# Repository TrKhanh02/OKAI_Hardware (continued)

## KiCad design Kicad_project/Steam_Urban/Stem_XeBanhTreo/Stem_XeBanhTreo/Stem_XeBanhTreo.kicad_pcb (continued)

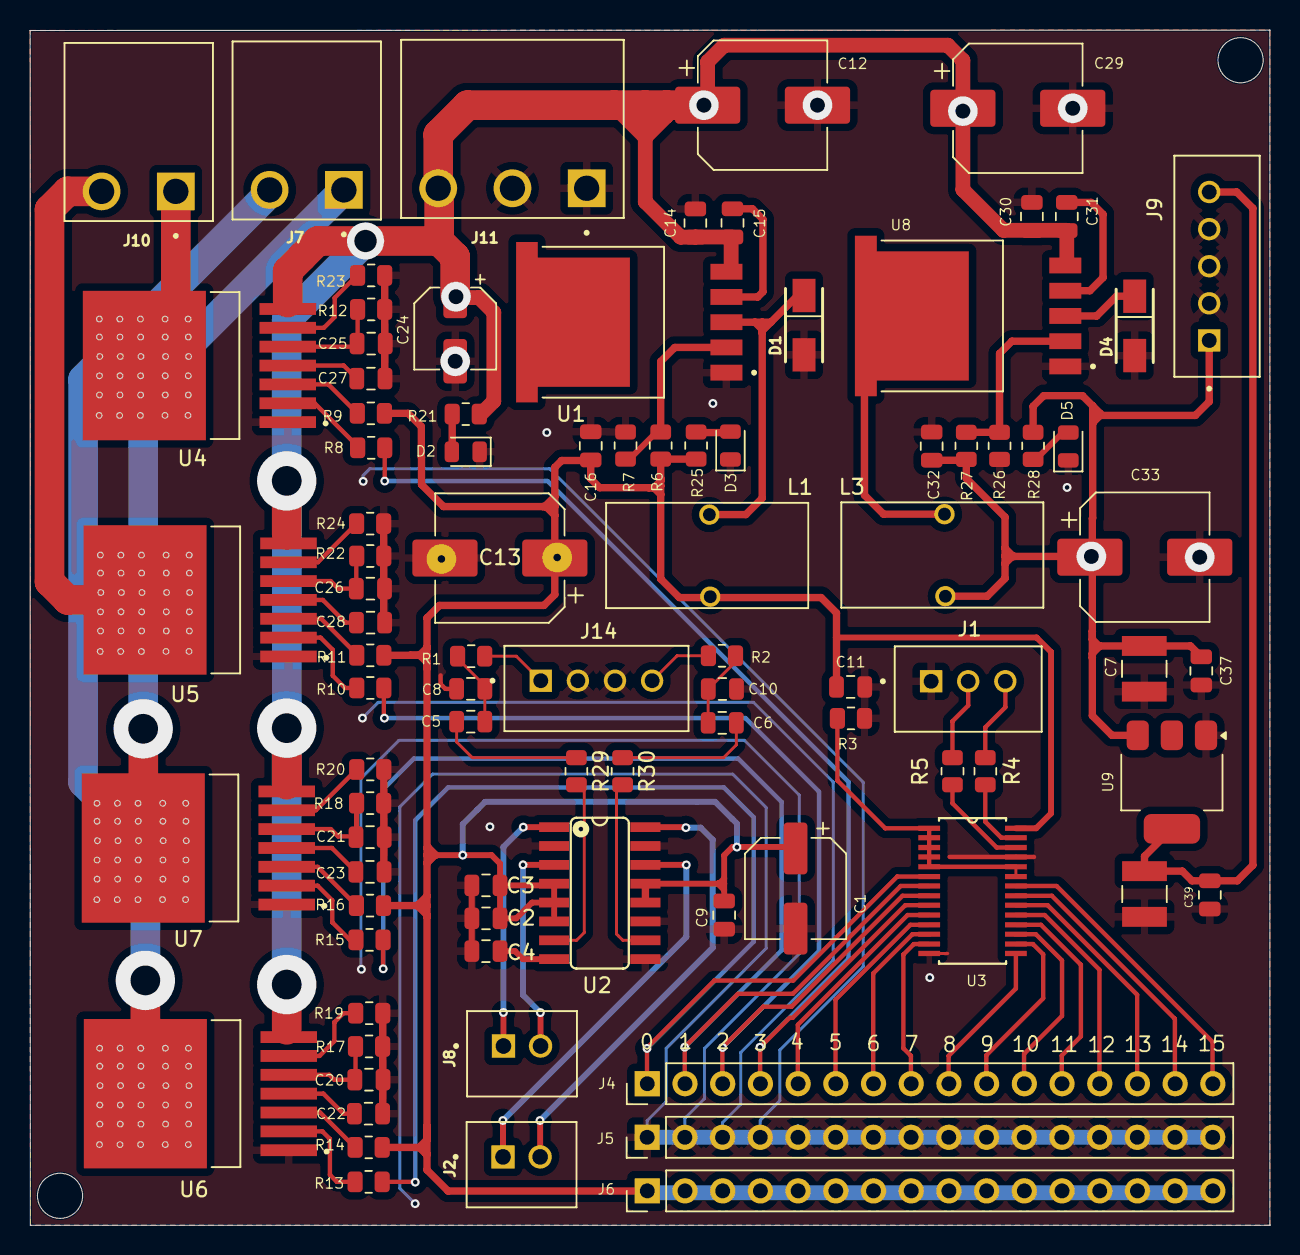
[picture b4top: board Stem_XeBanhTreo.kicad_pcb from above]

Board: 2 copper layers, 83.5 x 80.5 mm, 90 parts (0 on the bottom side), 68 nets.

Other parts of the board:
C17: 22uF/16V; CAPPC3528X210N
C39: 104; C_0805_2012Metric
J1: PCA9685; JST_B3B-XH-A
J14: B4B-XH-A; JST_B4B-XH-A

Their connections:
/SCL: J1.2; also elsewhere on the board
/SDA: J1.3; also elsewhere on the board
unnamed 32: J14.1; also elsewhere on the board
unnamed 33: J14.4; also elsewhere on the board

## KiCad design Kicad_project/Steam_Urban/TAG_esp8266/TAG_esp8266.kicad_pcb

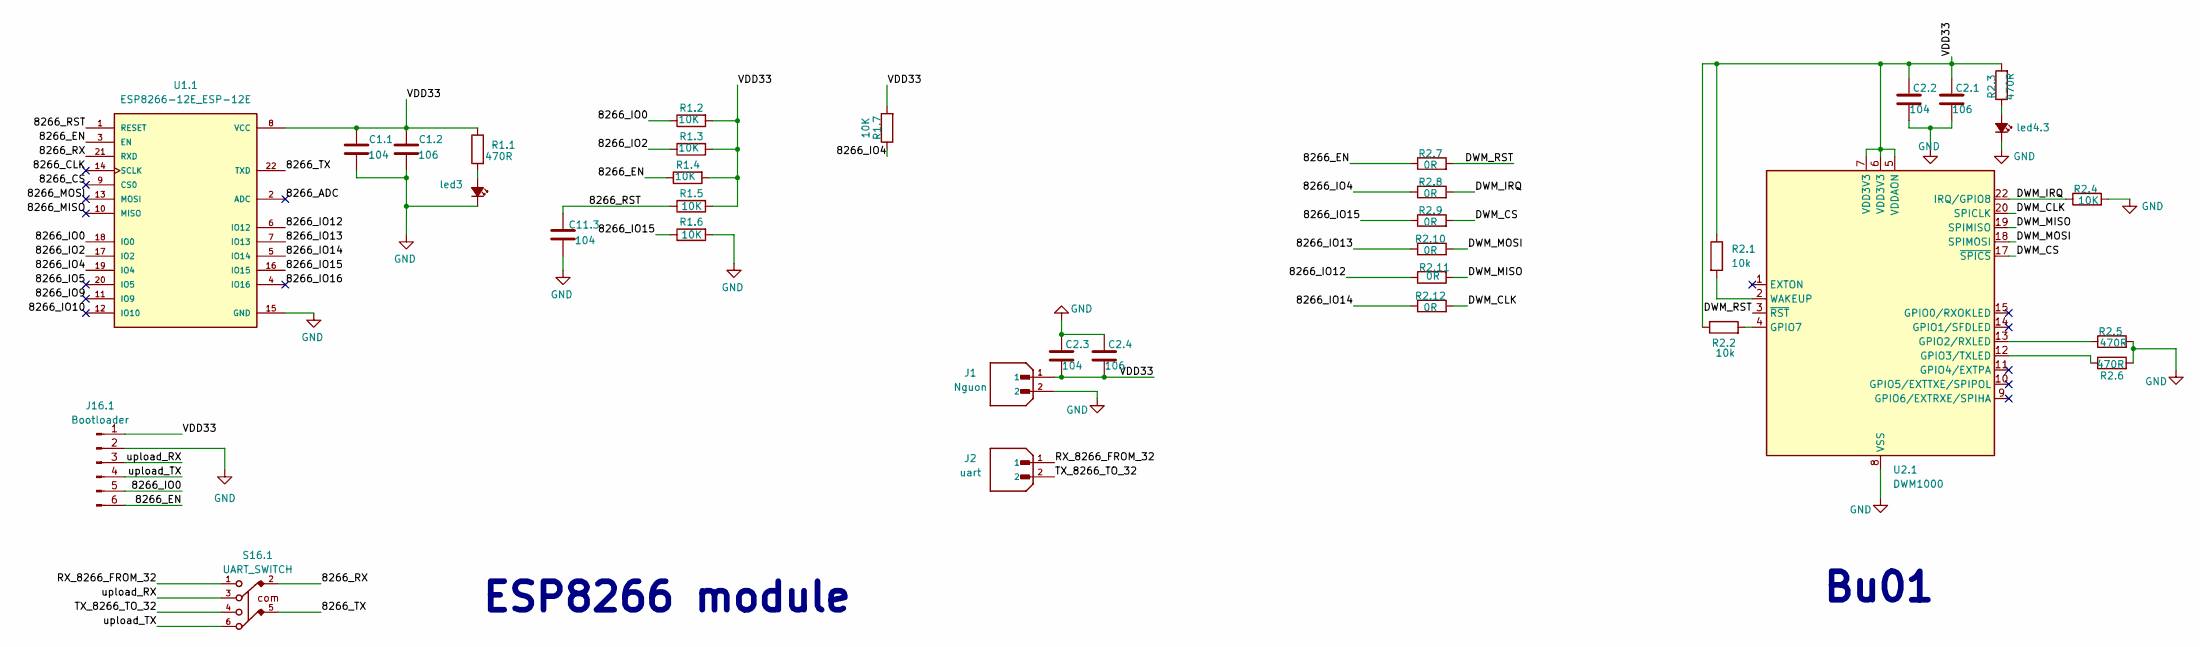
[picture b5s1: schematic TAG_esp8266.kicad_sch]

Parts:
C1.1, C2.2, C2.3, C11.3: 104; C_0805_2012Metric_Pad1.18x1.45mm_HandSolder
C1.2, C2.1, C2.4: 106; C_0805_2012Metric_Pad1.18x1.45mm_HandSolder
J1: Nguon; JST_B2B-XH-A_LF__SN_; PARTREV N/A
J2: uart; JST_B2B-XH-A_LF__SN_; PARTREV N/A
J16.1: Bootloader; PinSocket_1x06_P2.54mm_Vertical
R1.1, R2.3, R2.5, R2.6: 470R; R_0805_2012Metric_Pad1.20x1.40mm_HandSolder
R1.2, R1.3, R1.4, R1.5, R1.6, R1.7, R2.4: 10K; R_0805_2012Metric_Pad1.20x1.40mm_HandSolder
R2.1, R2.2: 10k; R_0805_2012Metric_Pad1.20x1.40mm_HandSolder
R2.7, R2.8, R2.9, R2.10, R2.11, R2.12: 0R; R_0805_2012Metric_Pad1.20x1.40mm_HandSolder
S16.1: UART_SWITCH; 452406020024
U1.1: ESP8266-12E_ESP-12E; XCVR_ESP8266-12E_ESP-12E
U2.1: DWM1000
led3, led4.3: LED_Small_Filled; LED_0805_2012Metric_Pad1.15x1.40mm_HandSolder

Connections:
/8266_ADC: U1.1.2 (ADC)
/8266_CLK: U1.1.14 (SCLK)
/8266_CS: U1.1.9 (CS0)
/8266_EN: J16.1.6, R1.4.1, R2.7.1, U1.1.3 (EN)
/8266_IO0: J16.1.5, R1.2.1, U1.1.18 (IO0)
/8266_IO2: R1.3.1, U1.1.17 (IO2)
/8266_IO4: R1.7.1, R2.8.1, U1.1.19 (IO4)
/8266_IO5: U1.1.20 (IO5)
/8266_IO9: U1.1.11 (IO9)
/8266_IO10: U1.1.12 (IO10)
/8266_IO12: R2.11.1, U1.1.6 (IO12)
/8266_IO13: R2.10.1, U1.1.7 (IO13)
/8266_IO14: R2.12.1, U1.1.5 (IO14)
/8266_IO15: R1.6.1, R2.9.1, U1.1.16 (IO15)
/8266_IO16: U1.1.4 (IO16)
/8266_MISO: U1.1.10 (MISO)
/8266_MOSI: U1.1.13 (MOSI)
/8266_RST: C11.3.1, R1.5.1, U1.1.1 (RESET)
/8266_RX: S16.1.2, U1.1.21 (RXD)
/8266_TX: S16.1.5, U1.1.22 (TXD)
/DWM_CLK: R2.12.2, U2.1.20 (SPICLK)
/DWM_CS: R2.9.2, U2.1.17 (~SPICS)
/DWM_IRQ: R2.4.1, R2.8.2, U2.1.22 (IRQ/GPIO8)
/DWM_MISO: R2.11.2, U2.1.19 (SPIMISO)
/DWM_MOSI: R2.10.2, U2.1.18 (SPIMOSI)
/DWM_RST: R2.7.2, U2.1.3 (~RST)
/RX_8266_FROM_32: J2.1, S16.1.1
/TX_8266_TO_32: J2.2, S16.1.4
/VDD33: C1.1.1, C1.2.1, C2.1.1, C2.2.1, C2.3.2, C2.4.2, J1.1, J16.1.1, R1.1.1, R1.2.2, R1.3.2, R1.4.2, R1.5.2, R1.7.2, R2.1.1, R2.2.1, R2.3.2, U1.1.8 (VCC), U2.1.5 (VDDAON), U2.1.6 (VDD3V3), U2.1.7 (VDD3V3)
/upload_RX: J16.1.3, S16.1.3
/upload_TX: J16.1.4, S16.1.6
GND: C1.1.2, C1.2.2, C2.1.2, C2.2.2, C2.3.1, C2.4.1, C11.3.2, J1.2, J16.1.2, R1.6.2, R2.4.2, R2.5.2, R2.6.2, U1.1.15 (GND), U2.1.8 (VSS), U2.1.16 (VSS), U2.1.21 (VSS), U2.1.23 (VSS), U2.1.24 (VSS), led3.1 (K), led4.3.1 (K)
unnamed: R2.5.1, U2.1.13 (GPIO2/RXLED)
unnamed: R2.6.1, U2.1.12 (GPIO3/TXLED)
unnamed: R2.2.2, U2.1.4 (GPIO7)
unnamed: R2.1.2, U2.1.2 (WAKEUP)
unnamed: R1.1.2, led3.2 (A)
unnamed: R2.3.1, led4.3.2 (A)

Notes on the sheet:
ESP8266 module
Bu01

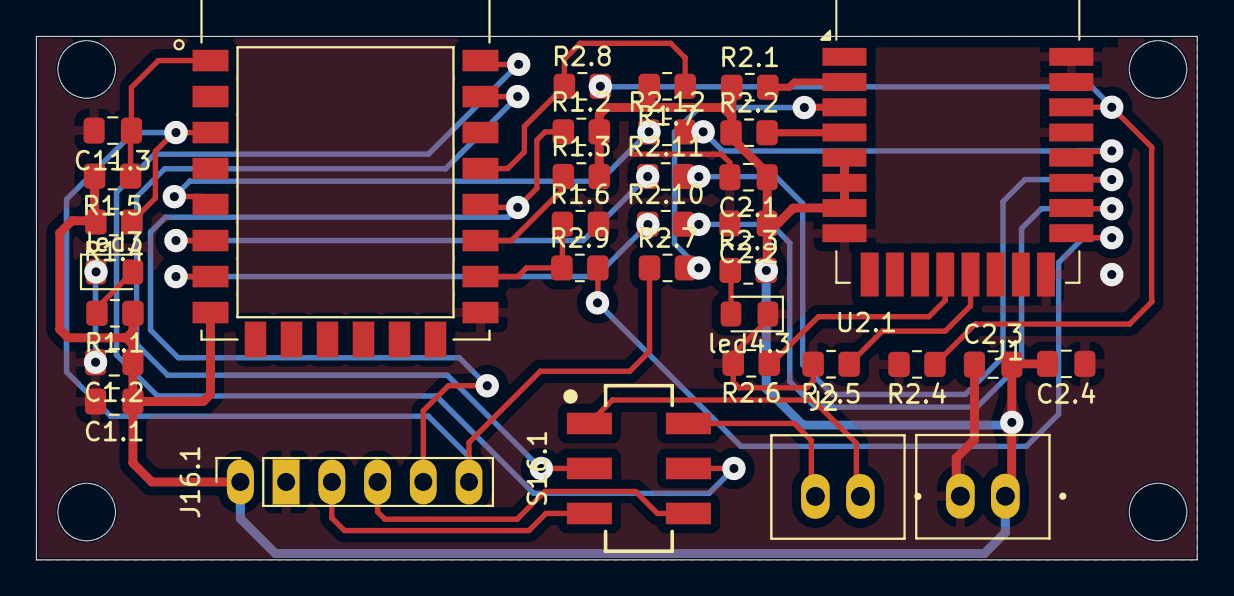
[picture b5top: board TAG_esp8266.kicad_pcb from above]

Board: 2 copper layers, 64.5 x 29.1 mm, 34 parts (0 on the bottom side), 29 nets.

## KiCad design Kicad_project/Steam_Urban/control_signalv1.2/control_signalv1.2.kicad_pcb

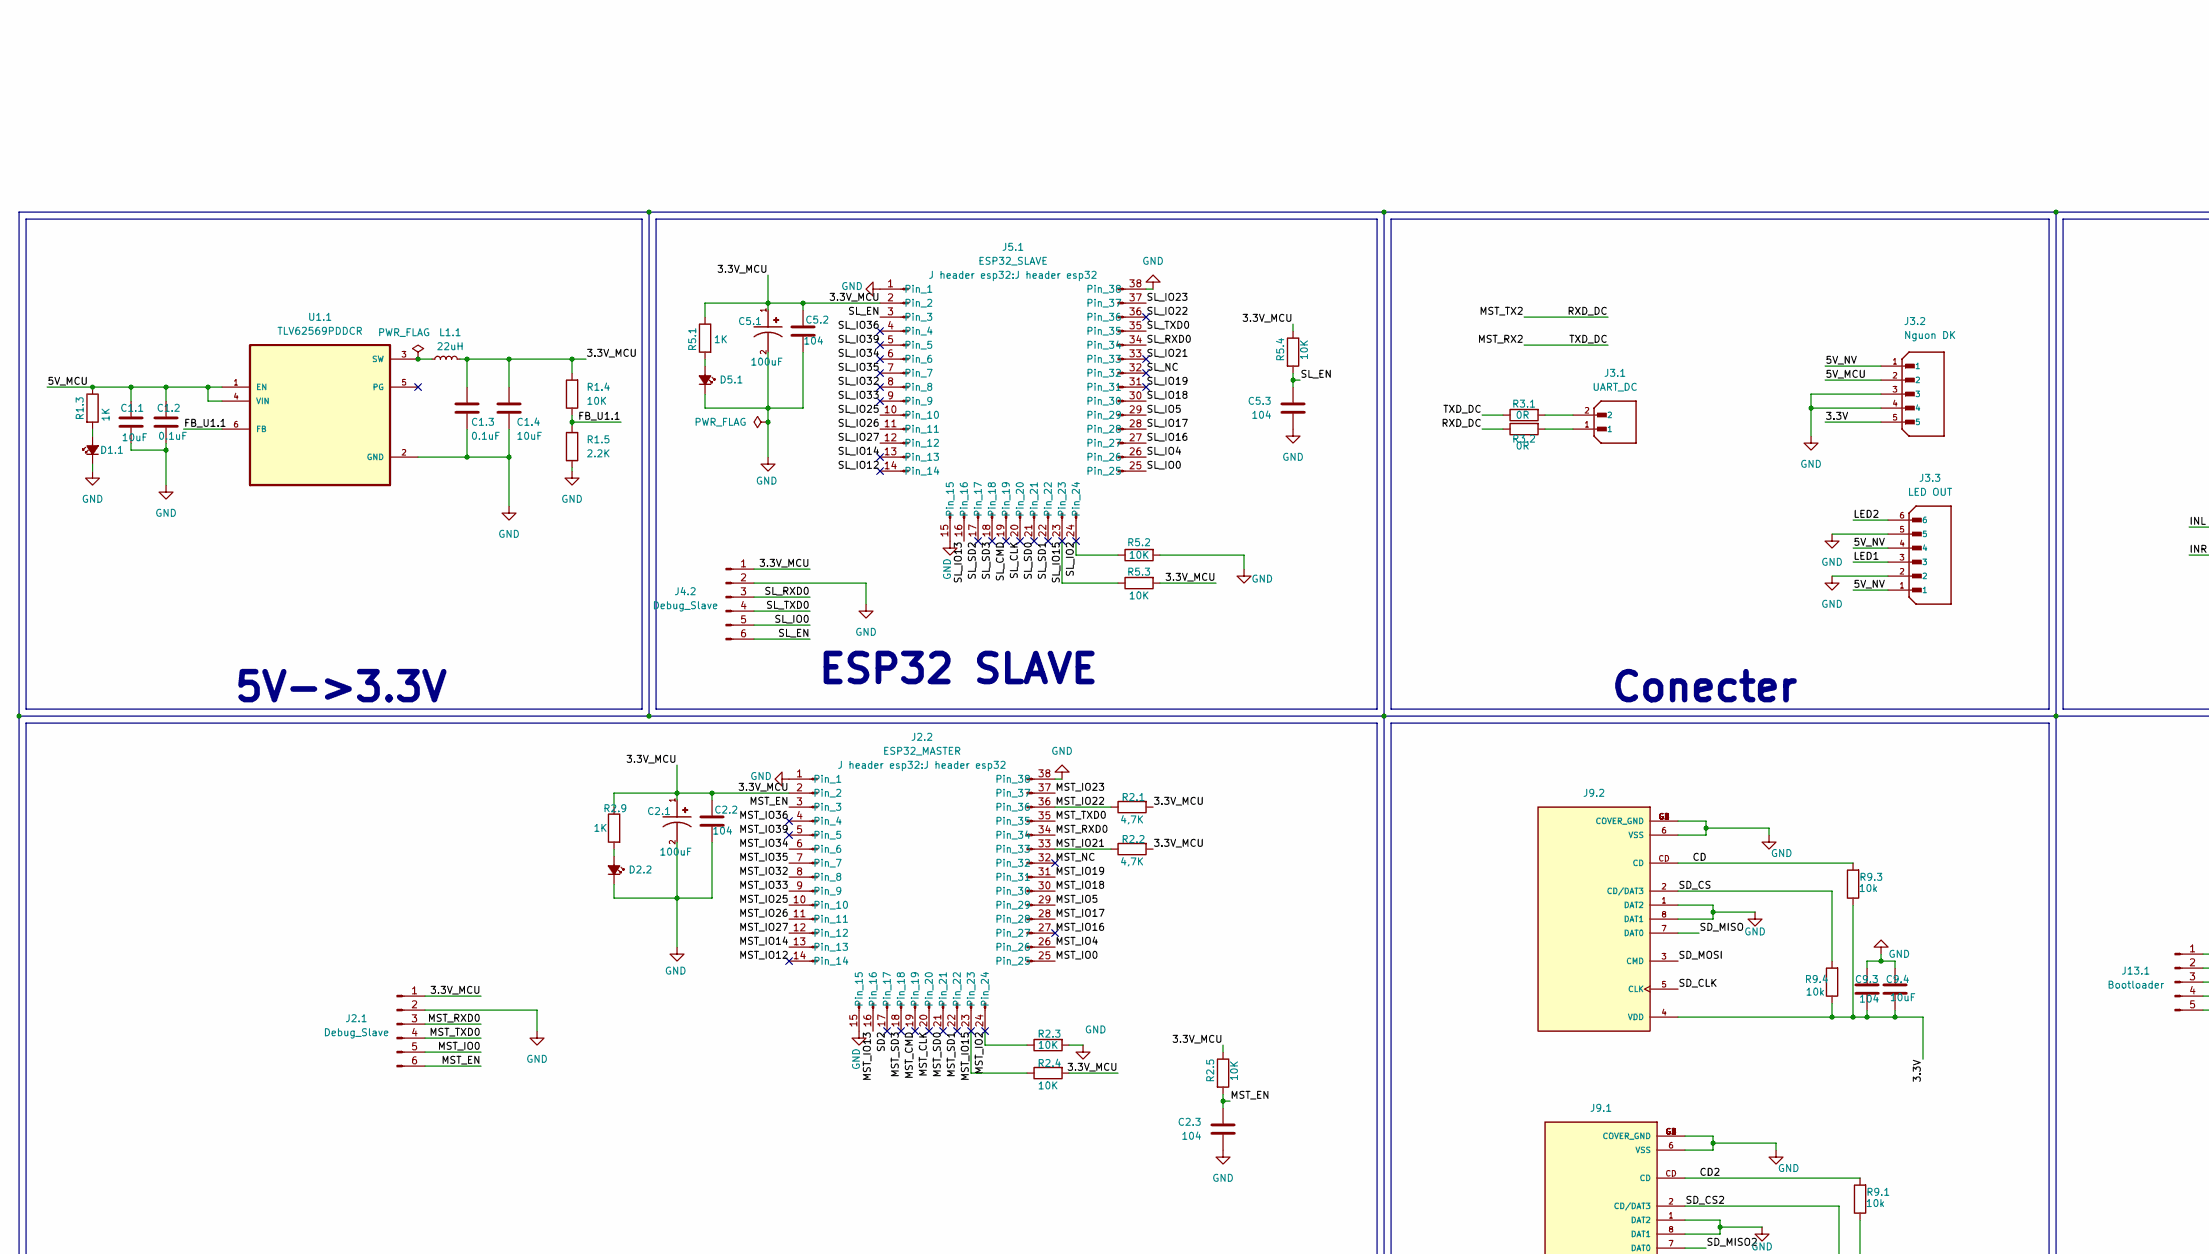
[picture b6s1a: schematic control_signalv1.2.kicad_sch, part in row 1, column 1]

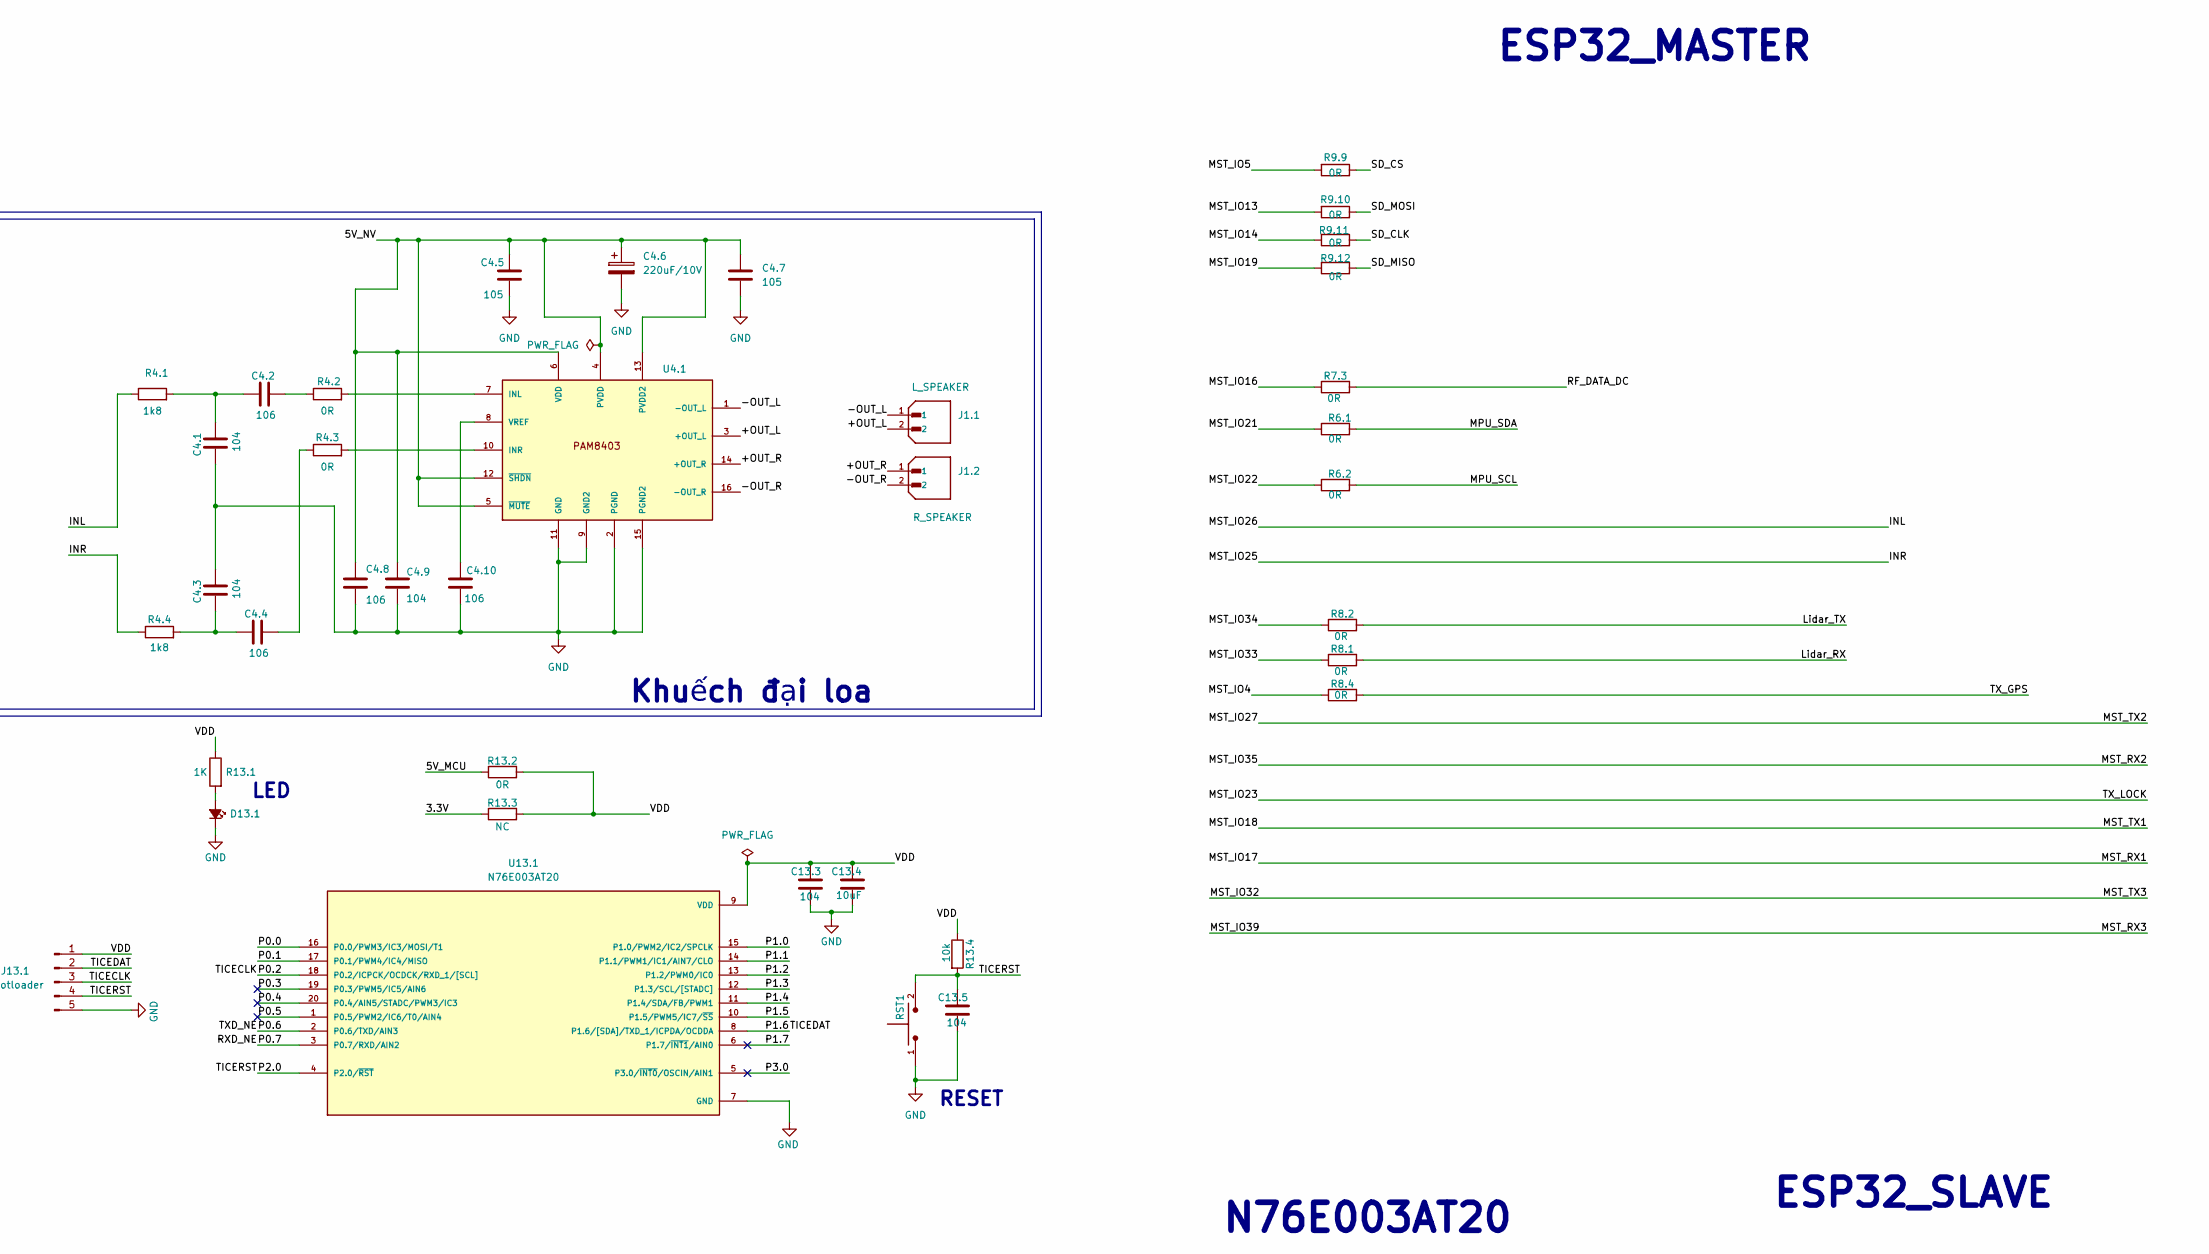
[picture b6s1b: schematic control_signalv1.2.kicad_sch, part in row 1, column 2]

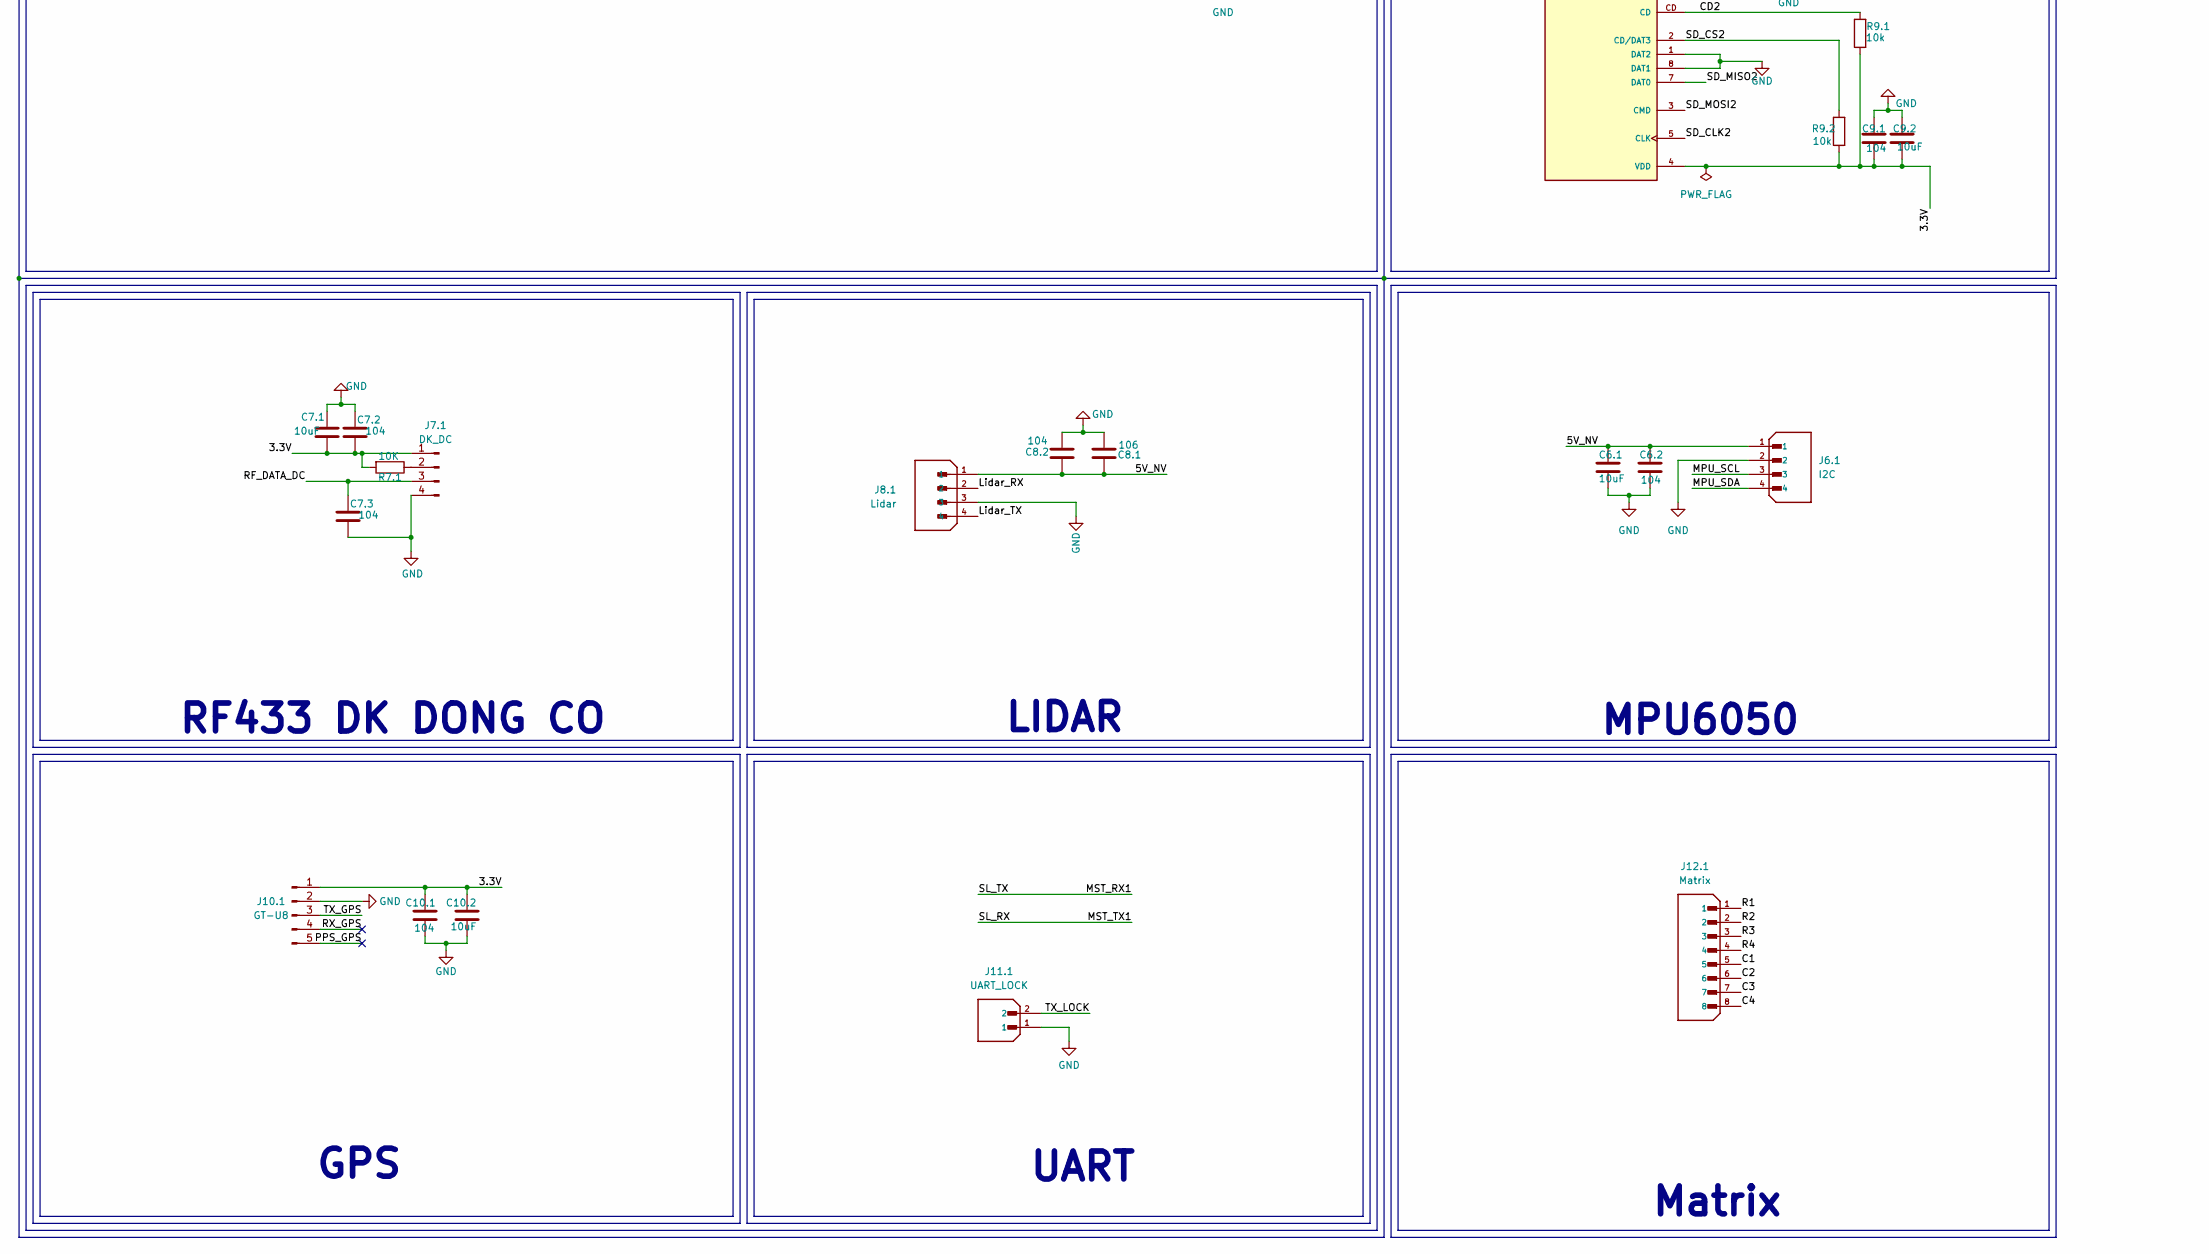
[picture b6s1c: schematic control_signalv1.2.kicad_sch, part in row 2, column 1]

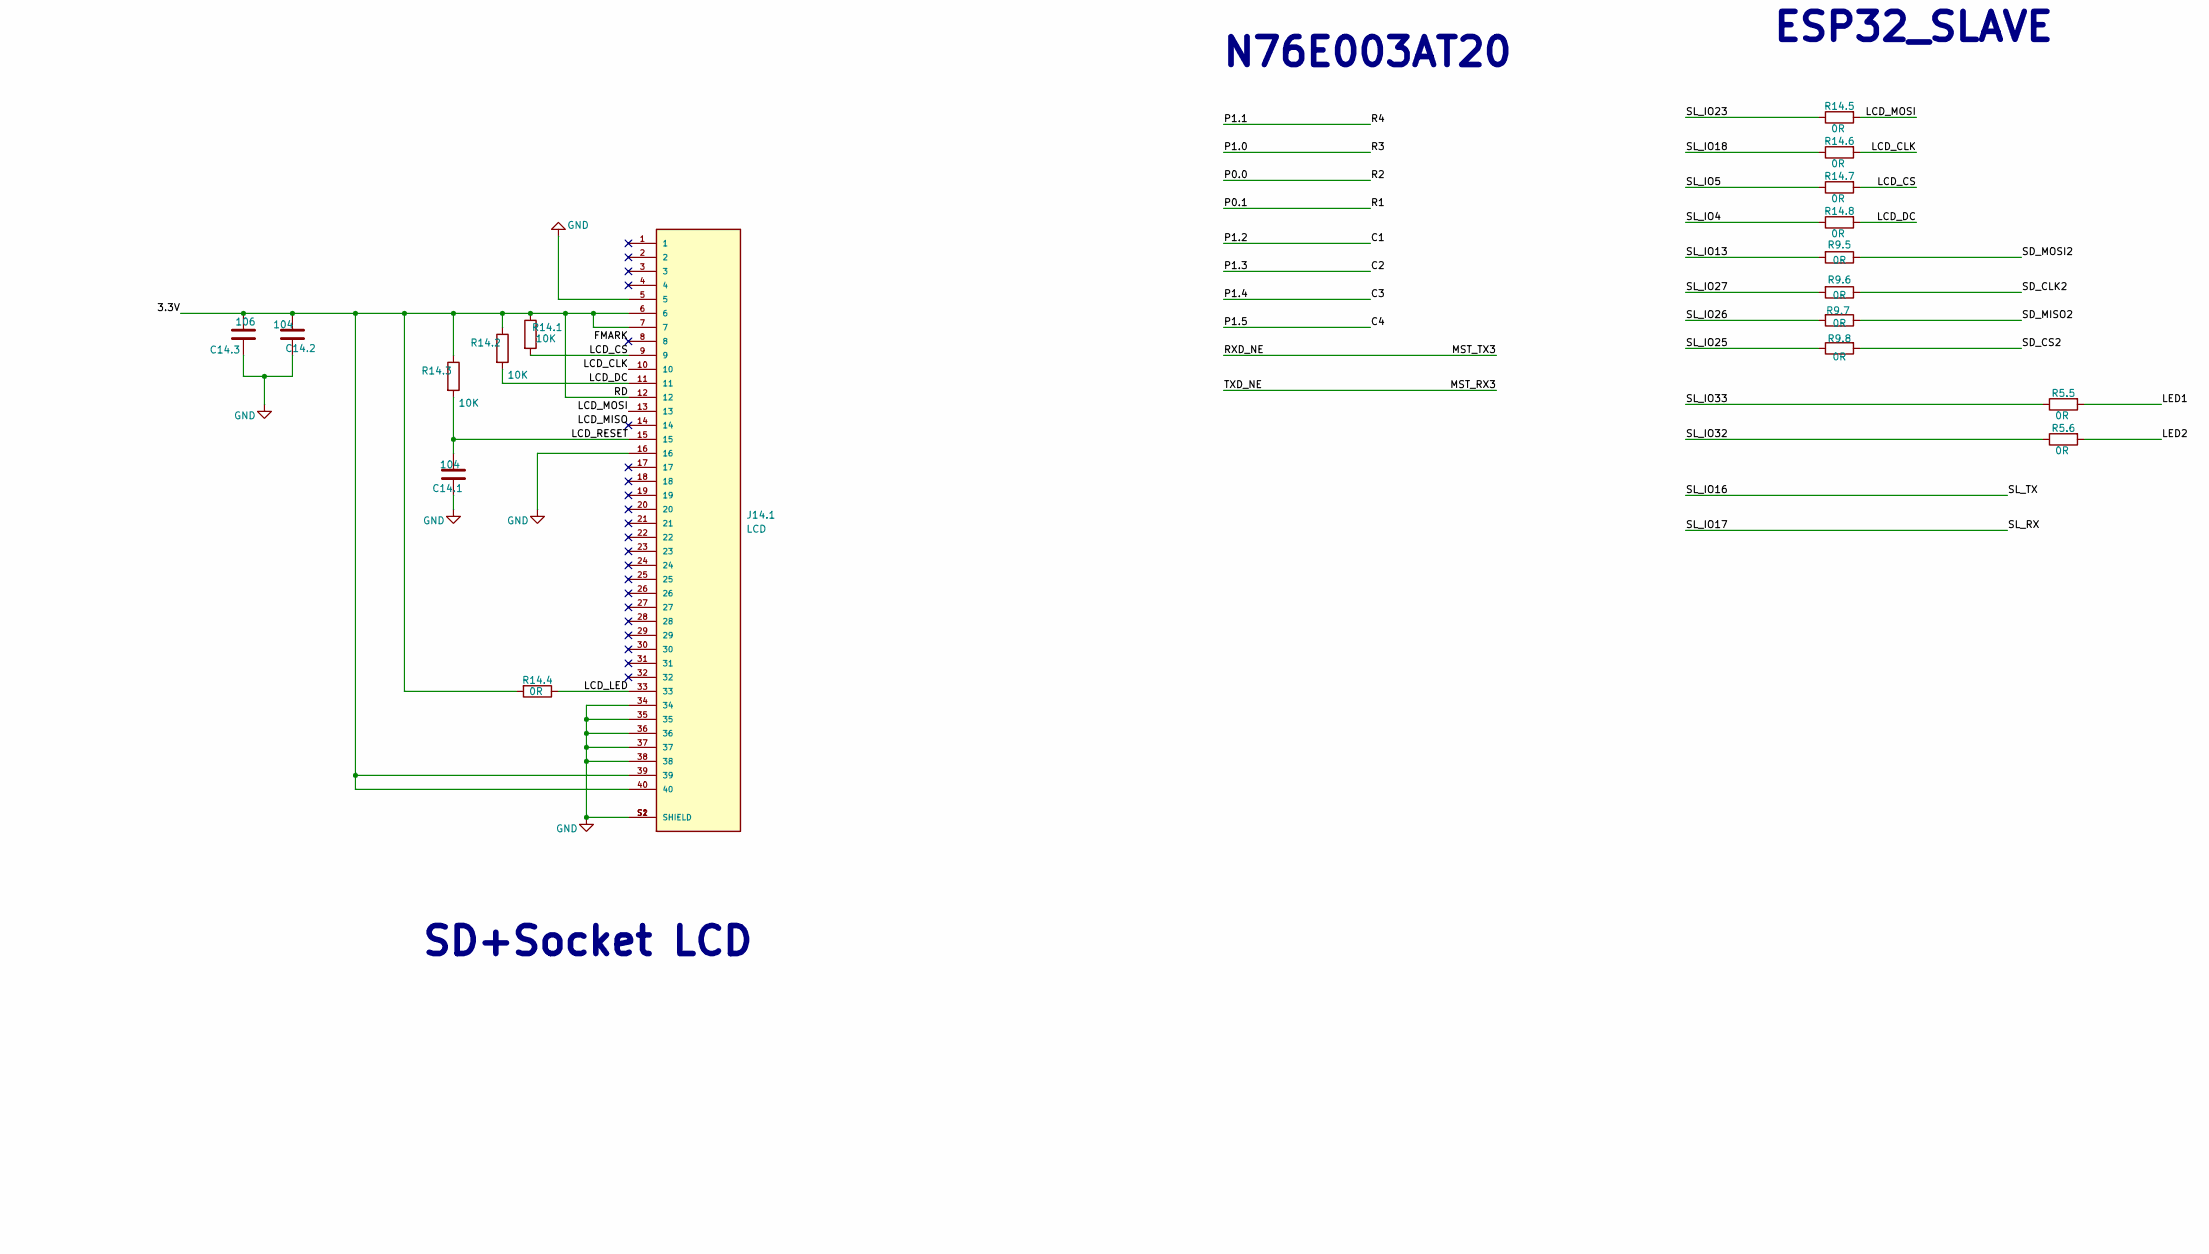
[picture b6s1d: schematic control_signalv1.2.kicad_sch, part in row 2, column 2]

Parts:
C1.1, C1.4: 10uF; C_0805_2012Metric
C1.2, C1.3: 0.1uF; C_0805_2012Metric
C2.1, C5.1: 100uF; CAPMP3216X180N; PARTREV 031320
C2.2, C2.3, C5.2, C5.3, C6.2, C7.2, C7.3, C8.2, C9.1, C9.3, C10.1, C13.3, C13.5, C14.1, C14.2: 104; C_0805_2012Metric_Pad1.18x1.45mm_HandSolder
C4.1, C4.3, C4.9: 104; C_0805_2012Metric
C4.2, C4.4, C4.8, C4.10: 106; C_0805_2012Metric
C4.5, C4.7: 105; C_0805_2012Metric
C4.6: 220uF/10V; CP_Elec_6.3x5.4
C6.1, C7.1, C9.2, C9.4, C10.2, C13.4: 10uF; C_0805_2012Metric_Pad1.18x1.45mm_HandSolder
C8.1, C14.3: 106; C_0805_2012Metric_Pad1.18x1.45mm_HandSolder
D1.1, D2.2, D5.1, D13.1: LED_Small_Filled; LED_0805_2012Metric_Pad1.15x1.40mm_HandSolder
J1.1: L_SPEAKER; JST_B2B-XH-A; PARTREV N/A
J1.2: R_SPEAKER; JST_B2B-XH-A; PARTREV N/A
J2.1, J4.2: Debug_Slave; PinSocket_1x06_P2.54mm_Vertical
J2.2: ESP32_MASTER; J header esp32
J3.1: UART_DC; JST_B2B-XH-A_LF__SN_; PARTREV N/A
J3.2: Nguon DK; JST_B5B-XH-A; PARTREV 7/4/21
J3.3: LED OUT; JST_B6B-XH-A_LF__SN_; PARTREV 7/4/21
J5.1: ESP32_SLAVE; J header esp32
J6.1: I2C; JST_B4B-XH-A_LF__SN_; PARTREV 7/4/21
J7.1: DK_DC; PinSocket_1x04_P2.54mm_Vertical
J8.1: Lidar; HRS_DF14-4P-1.25H_22_
J9.1, J9.2: SD; CUI_MSD-1-A; PARTREV 1.0
J10.1: GT-U8; PinSocket_1x05_P2.54mm_Vertical
J11.1: UART_LOCK; JST_B2B-XH-A_LF__SN_; PARTREV N/A
J12.1: Matrix; JST_B8B-XH-A_LF__SN_; PARTREV 7/4/21
J13.1: Bootloader; PinHeader_1x05_P2.54mm_Vertical
J14.1: LCD; TE_4-1734592-0; PARTREV C
L1.1: 22uH; L_Ferrocore_DLG-0705
R1.3, R2.9, R5.1, R13.1: 1K; R_0805_2012Metric_Pad1.20x1.40mm_HandSolder
R1.4: 10K; R_0805_2012Metric
R1.5: 2.2K; R_0805_2012Metric
R2.1, R2.2: 4,7K; R_0805_2012Metric_Pad1.20x1.40mm_HandSolder
R2.3, R2.4, R2.5, R5.2, R5.3, R5.4, R7.1, R14.1, R14.2, R14.3: 10K; R_0805_2012Metric_Pad1.20x1.40mm_HandSolder
R3.1, R3.2, R5.5, R5.6, R6.1, R6.2, R7.3, R8.1, R8.2, R8.4, R9.5, R9.6, R9.7, R9.8, R9.9, R9.10, R9.11, R9.12, R13.2, R14.4, R14.5, R14.6, R14.7, R14.8: 0R; R_0805_2012Metric_Pad1.20x1.40mm_HandSolder
R4.1, R4.4: 1k8; R_0805_2012Metric
R4.2, R4.3: 0R; R_0805_2012Metric
R9.1, R9.2, R9.3, R9.4, R13.4: 10k; R_0805_2012Metric_Pad1.20x1.40mm_HandSolder
R13.3: NC; R_0805_2012Metric_Pad1.20x1.40mm_HandSolder
RST1: TS10-63-26-BE-250-SMT-TR; SW_TS10-63-26-BE-250-SMT-TR; PARTREV 1.0
U1.1: TLV62569PDDCR; SOT95P280X110-6N
U4.1: PAM8403; SOP-16
U13.1: N76E003AT20; SOP65P640X120-20N; PARTREV 1.04

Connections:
/3.3V: C7.1.2, C7.2.2, C9.1.1, C9.2.1, C9.3.1, C9.4.1, C10.1.1, C10.2.1, C14.2.2, C14.3.2, J3.2.5, J7.1.1, J9.1.4 (VDD), J9.2.4 (VDD), J10.1.1, J14.1.6, J14.1.7, J14.1.12, J14.1.39, J14.1.40, R7.1.2, R9.1.1, R9.2.1, R9.3.1, R9.4.1, R13.3.1, R14.1.1, R14.2.1, R14.3.1, R14.4.2
/3.3V_MCU: C1.3.1, C1.4.1, C2.1.1, C2.2.1, C5.1.1, C5.2.1, J2.1.1, J2.2.2, J4.2.1, J5.1.2, L1.1.1, R1.4.2, R2.1.2, R2.2.2, R2.4.2, R2.5.1, R2.9.1, R5.1.1, R5.3.2, R5.4.1
/5V_MCU: C1.1.1, C1.2.1, J3.2.2, R1.3.1, R13.2.1, U1.1.1 (EN), U1.1.4 (VIN)
/5V_NV: C4.5.2, C4.6.1, C4.7.2, C4.8.2, C4.9.2, C6.1.1, C6.2.1, C8.1.1, C8.2.1, J3.2.1, J3.3.1, J3.3.4, J6.1.1, J8.1.1, U4.1.4 (PVDD), U4.1.5 (~MUTE), U4.1.6 (VDD), U4.1.12 (~SHDN), U4.1.13 (PVDD2)
/+OUT_L: J1.1.2, U4.1.3 (+OUT_L)
/+OUT_R: J1.2.1, U4.1.14 (+OUT_R)
/-OUT_L: J1.1.1, U4.1.1 (-OUT_L)
/-OUT_R: J1.2.2, U4.1.16 (-OUT_R)
/C1: J12.1.5, U13.1.13 (P1.2/PWM0/IC0)
/C2: J12.1.6, U13.1.12 (P1.3/SCL/[STADC])
/C3: J12.1.7, U13.1.11 (P1.4/SDA/FB/PWM1)
/C4: J12.1.8, U13.1.10 (P1.5/PWM5/IC7/~SS)
/CD: J9.2.CD, R9.3.2
/CD2: J9.1.CD, R9.1.2
/FB_U1.1: R1.4.1, R1.5.2, U1.1.6 (FB)
/FMARK: J14.1.8
/INL: J2.2.11, R4.1.1
/INR: J2.2.10, R4.4.1
/LCD_CLK: J14.1.10, R14.6.2
/LCD_CS: J14.1.9, R14.1.2, R14.7.2
/LCD_DC: J14.1.11, R14.2.2, R14.8.2
/LCD_LED: J14.1.33, R14.4.1
/LCD_MISO: J14.1.14
/LCD_MOSI: J14.1.13, R14.5.2
/LCD_RESET: C14.1.2, J14.1.15, R14.3.2
/LED1: J3.3.3, R5.5.2
/LED2: J3.3.6, R5.6.2
/Lidar_RX: J8.1.2, R8.1.2
/Lidar_TX: J8.1.4, R8.2.2
/MPU_SCL: J6.1.3, R6.2.2
/MPU_SDA: J6.1.4, R6.1.2
/MST_CLK: J2.2.20
/MST_CMD: J2.2.19
/MST_EN: C2.3.1, J2.1.6, J2.2.3, R2.5.2
/MST_IO0: J2.1.5, J2.2.25
/MST_IO2: J2.2.24, R2.3.1
/MST_IO4: J2.2.26, R8.4.1
/MST_IO5: J2.2.29, R9.9.2
/MST_IO12: J2.2.14
/MST_IO13: J2.2.16, R9.10.2
/MST_IO14: J2.2.13, R9.11.2
/MST_IO15: J2.2.23, R2.4.1
/MST_IO16: J2.2.27, R7.3.1
/MST_IO17: J2.2.28, J5.1.27
/MST_IO18: J2.2.30, J5.1.28
/MST_IO19: J2.2.31, R9.12.1
/MST_IO21: J2.2.33, R2.2.1, R6.1.1
/MST_IO22: J2.2.36, R2.1.1, R6.2.1
/MST_IO23: J2.2.37, J11.1.2
/MST_IO27: J2.2.12, R3.2.1
/MST_IO32: J2.2.8, U13.1.3 (P0.7/RXD/AIN2)
/MST_IO33: J2.2.9, R8.1.1
/MST_IO34: J2.2.6, R8.2.1
/MST_IO35: J2.2.7, R3.1.1
/MST_IO36: J2.2.4
/MST_IO39: J2.2.5, U13.1.2 (P0.6/TXD/AIN3)
/MST_NC: J2.2.32
/MST_RXD0: J2.1.3, J2.2.34
/MST_SD0: J2.2.21
/MST_SD1: J2.2.22
/MST_SD3: J2.2.18
/MST_TXD0: J2.1.4, J2.2.35
/P0.0: J12.1.2, U13.1.16 (P0.0/PWM3/IC3/MOSI/T1)
/P0.1: J12.1.1, U13.1.17 (P0.1/PWM4/IC4/MISO)
/P0.2: J13.1.3, U13.1.18 (P0.2/ICPCK/OCDCK/RXD_1/[SCL])
/P0.3: U13.1.19 (P0.3/PWM5/IC5/AIN6)
/P0.4: U13.1.20 (P0.4/AIN5/STADC/PWM3/IC3)
/P0.5: U13.1.1 (P0.5/PWM2/IC6/T0/AIN4)
/P1.0: J12.1.3, U13.1.15 (P1.0/PWM2/IC2/SPCLK)
/P1.1: J12.1.4, U13.1.14 (P1.1/PWM1/IC1/AIN7/CLO)
/P1.6: J13.1.2, U13.1.8 (P1.6/[SDA]/TXD_1/ICPDA/OCDDA)
/P1.7: U13.1.6 (P1.7/~INT1/AIN0)
/P2.0: C13.5.1, J13.1.4, R13.4.2, RST1.2, U13.1.4 (P2.0/~RST)
/P3.0: U13.1.5 (P3.0/~INT0/OSCIN/AIN1)
/PPS_GPS: J10.1.5
/RF_DATA_DC: C7.3.1, J7.1.3, R7.3.2
/RX_GPS: J10.1.4
/SD2: J2.2.17
/SD_CLK: J9.2.5 (CLK), R9.11.1
/SD_CLK2: J9.1.5 (CLK), R9.6.1
/SD_CS: J9.2.2 (CD/DAT3), R9.4.2, R9.9.1
/SD_CS2: J9.1.2 (CD/DAT3), R9.2.2, R9.8.2
/SD_MISO: J9.2.7 (DAT0), R9.12.2
/SD_MISO2: J9.1.7 (DAT0), R9.7.1
/SD_MOSI: J9.2.3 (CMD), R9.10.1
/SD_MOSI2: J9.1.3 (CMD), R9.5.1
/SL_CLK: J5.1.20
/SL_CMD: J5.1.19
/SL_EN: C5.3.1, J4.2.6, J5.1.3, R5.4.2
/SL_IO0: J4.2.5, J5.1.25
/SL_IO2: J5.1.24, R5.2.1
/SL_IO4: J5.1.26, R14.8.1
/SL_IO5: J5.1.29, R14.7.1
/SL_IO12: J5.1.14
/SL_IO13: J5.1.16, R9.5.2
/SL_IO14: J5.1.13
/SL_IO15: J5.1.23, R5.3.1
/SL_IO18: J5.1.30, R14.6.1
/SL_IO19: J5.1.31
/SL_IO21: J5.1.33
/SL_IO22: J5.1.36
/SL_IO23: J5.1.37, R14.5.1
/SL_IO25: J5.1.10, R9.8.1
/SL_IO26: J5.1.11, R9.7.2
/SL_IO27: J5.1.12, R9.6.2
/SL_IO32: J5.1.8, R5.6.1
/SL_IO33: J5.1.9, R5.5.1
/SL_IO34: J5.1.6
/SL_IO35: J5.1.7
/SL_IO36: J5.1.4
/SL_IO39: J5.1.5
/SL_NC: J5.1.32
/SL_RXD0: J4.2.3, J5.1.34
/SL_SD0: J5.1.21
/SL_SD1: J5.1.22
/SL_SD2: J5.1.17
/SL_SD3: J5.1.18
/SL_TXD0: J4.2.4, J5.1.35
/TX_GPS: J10.1.3, R8.4.2
/VDD: C13.3.1, C13.4.1, J13.1.1, R13.1.1, R13.2.2, R13.3.2, R13.4.1, U13.1.9 (VDD)
GND: C1.1.2, C1.2.2, C1.3.2, C1.4.2, C2.1.2, C2.2.2, C2.3.2, C4.1.2, C4.3.1, C4.5.1, C4.6.2, C4.7.1, C4.8.1, C4.9.1, C4.10.1, C5.1.2, C5.2.2, C5.3.2, C6.1.2, C6.2.2, C7.1.1, C7.2.1, C7.3.2, C8.1.2, C8.2.2, C9.1.2, C9.2.2, C9.3.2, C9.4.2, C10.1.2, C10.2.2, C13.3.2, C13.4.2, C13.5.2, C14.1.1, C14.2.1, C14.3.1, D1.1.1 (K), D2.2.1 (K), D5.1.1 (K), D13.1.1 (K), J2.1.2, J2.2.1, J2.2.15, J2.2.38, J3.2.3, J3.2.4, J3.3.2, J3.3.5, J4.2.2, J5.1.1, J5.1.15, J5.1.38, J6.1.2, J7.1.4, J8.1.3, J9.1.1 (DAT2), J9.1.6 (VSS), J9.1.8 (DAT1), J9.1.G1 (COVER_GND), J9.1.G2 (COVER_GND), J9.1.G3 (COVER_GND), J9.1.G4 (COVER_GND), J9.2.1 (DAT2), J9.2.6 (VSS), J9.2.8 (DAT1), J9.2.G1 (COVER_GND), J9.2.G2 (COVER_GND), J9.2.G3 (COVER_GND), J9.2.G4 (COVER_GND), J10.1.2, J11.1.1, J13.1.5, J14.1.5, J14.1.16, J14.1.34, J14.1.35, J14.1.36, J14.1.37, J14.1.38, J14.1.S1 (SHIELD), J14.1.S2 (SHIELD), R1.5.1, R2.3.2, R5.2.2, RST1.1, U1.1.2 (GND), U4.1.2 (PGND), U4.1.9 (GND2), U4.1.11 (GND), U4.1.15 (PGND2), U13.1.7 (GND)
unnamed: C4.1.1, C4.2.2, R4.1.2
unnamed: C4.2.1, R4.2.1
unnamed: C4.3.2, C4.4.2, R4.4.2
unnamed: C4.4.1, R4.3.1
unnamed: D1.1.2 (A), R1.3.2
unnamed: D2.2.2 (A), R2.9.2
unnamed: D5.1.2 (A), R5.1.2
unnamed: D13.1.2 (A), R13.1.2
unnamed: J3.1.1, R3.2.2
unnamed: J3.1.2, R3.1.2
unnamed: J7.1.2, R7.1.1
unnamed: L1.1.2, U1.1.3 (SW)
unnamed: R4.2.2, U4.1.7 (INL)
unnamed: R4.3.2, U4.1.10 (INR)
unnamed: C4.10.2, U4.1.8 (VREF)

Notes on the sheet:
Conecter
MPU6050
UART
ESP32_MASTER
RESET
RF433 DK DONG CO
Khuếch đại loa
SD+Socket LCD
LIDAR
ESP32_SLAVE
5V->3.3V
LED
Matrix
N76E003AT20
ESP32 SLAVE
GPS
